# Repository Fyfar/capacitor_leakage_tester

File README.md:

# Capacitor Leakage Tester

> ⚠️ **Work in Progress** — this project is not yet complete.

A DIY high-sensitivity capacitor leakage current meter. Applies a selectable test
voltage to a capacitor under test and measures the resulting leakage current down
to the microamp range.

## Hardware

| Component | Part |
|-----------|------|
| MCU | RP2040-Zero |
| External ADC | ADS1115 (16-bit, I²C) |
| Display | HD44780 16×2 LCD (I²C) |
| Input | Rotary encoder |
| Test voltages | 10 V / 16 V / 25 V / 50 V |

KiCAD schematic and PCB files are in the [`kicad/`](kicad/) directory.

## Firmware

Built with [PlatformIO](https://platformio.org/) and the Arduino framework (Earle Philhower RP2040 core).

## Status

- [x] Schematic design
- [x] PCB layout
- [x] Firmware (core measurement loop)
- [ ] Pass/fail logic
- [ ] Testing & calibration
- [ ] Documentation

## License

[MIT](LICENSE)

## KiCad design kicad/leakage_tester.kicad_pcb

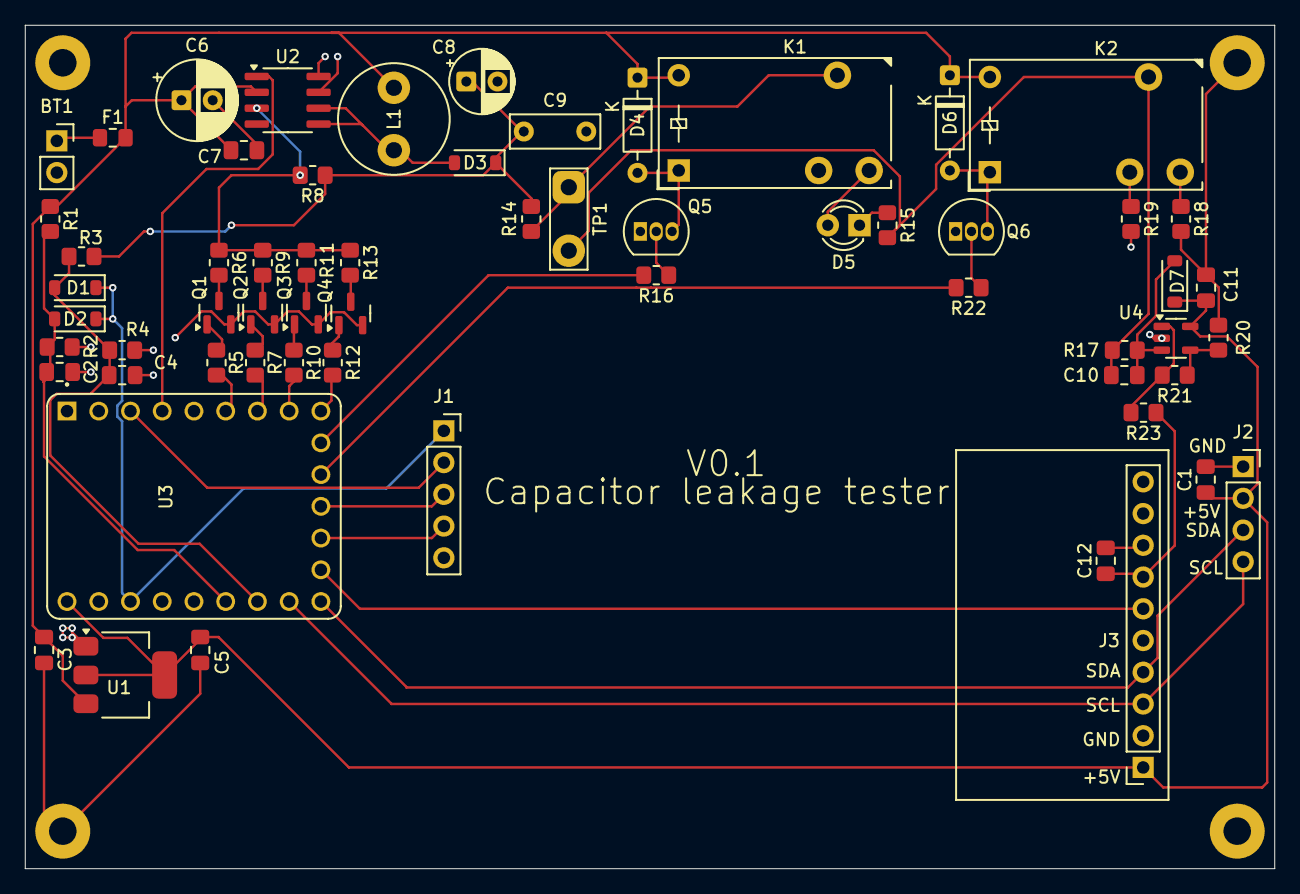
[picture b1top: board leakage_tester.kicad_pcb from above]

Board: 2 copper layers, 100.0 x 67.5 mm, 65 parts (0 on the bottom side), 45 nets.

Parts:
BT1: Battery 2s; PinSocket_1x02_P2.54mm_Vertical
C1, C2, C4, C7, C10, C11: 0.1u; C_0805_2012Metric_Pad1.18x1.45mm_HandSolder
C3, C5: 1u; C_0805_2012Metric_Pad1.18x1.45mm_HandSolder
C6: 16v 47u; CP_Radial_D6.3mm_P2.50mm
C8: 100v 4.7u; CP_Radial_D5.0mm_P2.50mm
C9: 0.1u; C_Rect_L7.0mm_W2.5mm_P5.00mm
C12: 0.22u; C_0805_2012Metric_Pad1.18x1.45mm_HandSolder
D1, D2, D3, D7: BAT46W; D_SOD-123
D4, D6: 1n4148; D_DO-35_SOD27_P7.62mm_Horizontal
D5: RED; LED_D3.0mm
F1: 200mA; Fuse_0805_2012Metric_Pad1.15x1.40mm_HandSolder
H1, H2, H3, H4: MountingHole; MountingHole_2.2mm_M2_Pad
J1: Encoder; PinSocket_1x05_P2.54mm_Vertical
J2: LCD; PinSocket_1x04_P2.54mm_Vertical
J3: ADS1115 ADC; PinSocket_1x10_P2.54mm_Vertical
K1, K2: Relay_SPDT; Relay_SPDT_18.4x10.2
L1: 33uH; L_Radial_D8.7mm_P5.00mm_Fastron_07HCP
Q1, Q2, Q3, Q4: 2N7002; SOT-23
Q5, Q6: 2N3904; TO-92_Inline
R1: 6.8k; R_0805_2012Metric_Pad1.20x1.40mm_HandSolder
R2: 3.3k; R_0805_2012Metric_Pad1.20x1.40mm_HandSolder
R3, R8: 100k; R_0805_2012Metric_Pad1.20x1.40mm_HandSolder
R4: 4.7k; R_0805_2012Metric_Pad1.20x1.40mm_HandSolder
R5, R7, R10, R12: 10k; R_0805_2012Metric_Pad1.20x1.40mm_HandSolder
R6: 14.2k; R_0805_2012Metric_Pad1.20x1.40mm_HandSolder
R9: 8.4k; R_0805_2012Metric_Pad1.20x1.40mm_HandSolder
R11: 5.2k; R_0805_2012Metric_Pad1.20x1.40mm_HandSolder
R13: 2.6k; R_0805_2012Metric_Pad1.20x1.40mm_HandSolder
R14, R16, R22: 2.2k; R_0805_2012Metric_Pad1.20x1.40mm_HandSolder
R15, R20: 3k; R_0805_2012Metric_Pad1.20x1.40mm_HandSolder
R17: 2.8k; R_0805_2012Metric_Pad1.20x1.40mm_HandSolder
R18: 1k 1%; R_0805_2012Metric_Pad1.20x1.40mm_HandSolder
R19: 10 1%; R_0805_2012Metric_Pad1.20x1.40mm_HandSolder
R21: 56k; R_0805_2012Metric_Pad1.20x1.40mm_HandSolder
R23: 100; R_0805_2012Metric_Pad1.20x1.40mm_HandSolder
TP1: DUT; TestPoint_2Pads_Pitch5.08mm_Drill1.3mm
U1: AMS1117-5; SOT-223-3_TabPin2
U2: XL6007; SOIC-8_3.9x4.9mm_P1.27mm
U3: RP2040-ZERO; MODULE_RP2040-ZERO
U4: AD8605; SOT-23-5

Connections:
+3.3V: D1.1 (K), D2.1 (K), J1.1, U3.21 (3V3)
+5V: C1.1, C5.1, C11.1, D7.1 (K), J2.2, J3.1, U1.2 (VO), U3.23 (5V), U4.5 (V+)
+BATT: C3.1, C6.1, C7.1, D4.1 (K), D6.1 (K), F1.2, K1.A2, K2.A2, L1.1, R1.1, U1.3 (VI), U2.2 (VIN)
/ADC_BATT: C2.1, D1.2 (A), R1.2, R2.1, U3.18 (GP27)
/ADC_DUT: C12.1, J3.7, R23.1
/ADC_HV: C4.1, D2.2 (A), R3.2, R4.1, U3.17 (GP26)
/ADC_RDY: J3.6, U3.14 (GP13)
/DISCHARGE_RELAY: R16.2, U3.10 (GP9)
/EN: U2.1 (EN), U3.4 (GP3)
/ENC_A: J1.3, U3.12 (GP11)
/ENC_B: J1.2, U3.3 (GP2)
/ENC_BTN: J1.4, U3.13 (GP12)
/R_10V: R5.2, U3.6 (GP5)
/R_16V: R7.2, U3.7 (GP6)
/R_25V: R10.2, U3.8 (GP7)
/R_50V: R12.2, U3.9 (GP8)
/SCL: J2.4, J3.3, U3.16 (GP15)
/SDA: J2.3, J3.4, U3.15 (GP14)
/SHUNT_RELAY: R22.2, U3.11 (GP10)
GND: BT1.2 (-), C1.2, C2.2, C3.2, C4.2, C5.2, C6.2, C7.2, C8.2, C9.2, C11.2, C12.2, H1.1, H2.1, H3.1, H4.1, J1.5, J2.1, J3.2, J3.5, J3.8, Q1.2 (S), Q2.2 (S), Q3.2 (S), Q4.2 (S), Q5.1 (E), Q6.1 (E), R2.2, R4.2, R18.2, R19.2, R20.2, U1.1 (GND), U2.7 (GND), U2.8 (GND), U3.22 (GND), U4.2 (V-)
unnamed: BT1.1 (+), F1.1
unnamed: D3.2 (A), L1.2, U2.5 (SW), U2.6 (SW)
unnamed: D4.2 (A), K1.A1, Q5.3 (C)
unnamed: D5.2 (A), K1.14
unnamed: D5.1 (K), R15.1
unnamed: D6.2 (A), K2.A1, Q6.3 (C)
unnamed: C10.2, D7.2 (A), R17.2, U4.3 (+)
unnamed: K1.11, R14.2, TP1.1
unnamed: K2.12, R19.1
unnamed: K2.14, R18.1
unnamed: Q1.3 (D), R6.2
unnamed: Q1.1 (G), R5.1
unnamed: Q2.3 (D), R9.2
unnamed: Q2.1 (G), R7.1
unnamed: Q3.3 (D), R11.2
unnamed: Q3.1 (G), R10.1
unnamed: Q4.3 (D), R13.2
unnamed: Q4.1 (G), R12.1
unnamed: Q5.2 (B), R16.1
unnamed: Q6.2 (B), R22.1
unnamed: R21.2, R23.2, U4.1
unnamed: R6.1, R8.2, R9.1, R11.1, R13.1, U2.3 (FB)
unnamed: R20.1, R21.1, U4.4 (-)
V_SHUNT: C10.1, K2.11, R15.2, R17.1, TP1.2
Vdrive: C8.1, C9.1, D3.1 (K), R3.1, R8.1, R14.1

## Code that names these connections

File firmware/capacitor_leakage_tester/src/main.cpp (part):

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constexpr float LOW_VOLTAGE_TO_INCREASE_GAIN = 43.0f;  // mV, ~200uA on low shunt

constexpr uint8_t DC_DC_ENABLE = 3;
constexpr uint8_t R_10V = 5;
constexpr uint8_t R_16V = 6;
constexpr uint8_t R_25V = 7;
constexpr uint8_t R_50V = 8;
constexpr uint8_t DISCHARGE_RELAY_PIN = 9;
constexpr uint8_t SHUNT_RELAY_PIN = 10;
constexpr uint8_t ADC_BATTERY_PIN = 27;
constexpr uint8_t ADC_OUTPUT_PIN = 26;

constexpr uint8_t dividerPins[4] = {R_10V, R_16V, R_25V, R_50V};

constexpr adsGain_t adcGain[5] = {GAIN_ONE, GAIN_TWO, GAIN_FOUR, GAIN_EIGHT, GAIN_SIXTEEN};

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
void dischargeCapacitor(EBAction action) {
    if (action == EBAction::Hold) {
        digitalWrite(DISCHARGE_RELAY_PIN, HIGH);  // Activate discharge relay
        digitalWrite(DC_DC_ENABLE, LOW);          // Disable DC-DC converter while discharging
    } else if (action == EBAction::ReleaseHold) {
        digitalWrite(DISCHARGE_RELAY_PIN, LOW);  // Deactivate discharge relay
    }
}

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}

void highLeakageShuntEnable() {
    digitalWrite(SHUNT_RELAY_PIN, LOW);  // Turn off shunt relay
}

void lowLeakageShuntEnable() {
    digitalWrite(SHUNT_RELAY_PIN, HIGH);  // Activate shunt relay
}

bool isADCGainTuned(int16_t adcValue) {
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        return;
    }

    bool isHighLeakageShunt = digitalRead(SHUNT_RELAY_PIN) == LOW;
    float voltage = adc.computeVolts(adcLeakage) * 1000.0f;  // in mV

    bool shuntSwithNeeded = false;
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
        lcd.setCursor(0, 1);

        bool uARange = digitalRead(SHUNT_RELAY_PIN) == HIGH;

        lcd.print(leakageCurrent * (uARange ? 1000.0f : 1.0f), 2);
        lcd.print(uARange ? " uA" : " mA");
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    Wire1.setSCL(15);

    pinMode(DC_DC_ENABLE, OUTPUT);         // DC-DC enable
    pinMode(R_10V, OUTPUT);                // R_10V
    pinMode(R_16V, OUTPUT);                // R_16V
    pinMode(R_25V, OUTPUT);                // R_25V
    pinMode(R_50V, OUTPUT);                // R_50V
    pinMode(DISCHARGE_RELAY_PIN, OUTPUT);  // DISCHARGE_RELAY
    pinMode(SHUNT_RELAY_PIN, OUTPUT);      // SHUNT_RELAY

    pinMode(ADC_OUTPUT_PIN, INPUT);   // ADC output
    pinMode(ADC_BATTERY_PIN, INPUT);  // ADC battery
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
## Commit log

2026-06-11 Add project files: firmware and PCB design
